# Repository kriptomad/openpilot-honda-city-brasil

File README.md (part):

# openpilot for the Honda City G7 (2023, Brazil)

[Versao em portugues: README.pt-BR.md](README.pt-BR.md)

An end-to-end, open effort to run openpilot / flowpilot on a 7th generation Honda City
(2023, Brazilian market, Honda Sensing camera-only "Bosch radarless", classic CAN, Bosch B
harness) using black panda class hardware (STM32F413), together with a from-scratch
**Hybrid Panda** PCB design (STM32H725, CAN-FD capable, black panda form factor) intended
as future hardware. The repository collects the hardware design, the panda firmware trees,
the car ports for two software stacks, the flashing procedure and every audit and report
produced along the way.

Author: Bruno Costa ([kriptomad](https://github.com/kriptomad)). This project is not
affiliated with, endorsed by or supported by comma.ai, Honda or any of the upstream authors.

**Nothing in this repository has been validated on real hardware or in a car.** Every
status below describes static analysis, compilation or continuous-integration results only.
No board has been fabricated, no panda has been flashed, no car has been fingerprinted.

## Status at a glance

| Track | Where | Status (honest) |
|---|---|---|
| Hybrid Panda PCB (STM32H725ZGT6, 4 layers) | [hardware/hybrid-panda](hardware/hybrid-panda) | Design complete and software-verified (2026-10-29): DRC 0 clearance / 0 unconnected / 0 shorts / 0 parity, 73 remaining items all intentional `lib_footprint_mismatch`; ERC 0 errors; gerber-rebuilt connectivity 0 short / 0 open; independent pin-by-pin review against the panda firmware. **Not physically verified**; bare-PCB order at the owner's discretion. Nothing built. |
| panda firmware `revive-f4` (black panda on current panda master) | [firmware/panda-revive-f4](firmware/panda-revive-f4) (submodule) | Compiles (debug and release), MISRA clean, `test.sh` green on the fork. Never executed on a board. |
| pandarevive (openpilot master host side for the black panda) | [docs/pandarevive.md](docs/pandarevive.md), repo [kriptomad/pandarevive](https://github.com/kriptomad/pandarevive) | openpilot branch `revive-f4` (4 commits on commaai master `0152aab4`): USB transport back in `pandad`, external panda flashing, tests. openpilot CI green on GitHub-hosted runners. Never executed on a board. |
| panda firmware `hybrid-h725` (Hybrid Panda target) | [firmware/panda-hybrid-h725](firmware/panda-hybrid-h725) (submodule) | Compiles (`panda_h7`, `panda_h7_hybrid`, `panda_h7_ldo`), MISRA clean. Never executed on a board (no board exists). |
| openpilot v0.9.9 Honda City port | [software/openpilot-v0.9.9-city-g7](software/openpilot-v0.9.9-city-g7) + [software/opendbc-v0.9.9-city-g7](software/opendbc-v0.9.9-city-g7) (submodules) | Port complete, two independent audits, CI green on the fork (static, build, unit, cars 0-3; process replay differs only by the expected `carParams.flags` bit). Untested in a car. |
| flowpilot standalone APK | [software/flowpilot-city-g7](software/flowpilot-city-g7) (submodule) | APK builds in GitHub Actions. Boots on a Samsung Galaxy S24 Ultra up to "waiting for controls" without a panda. Untested with a panda or a car. |
| Flashing guides | [docs/flashing](docs/flashing) | Written from the code and the PCB files. Not executed on hardware. |

## Safety disclaimer

This is an unvalidated, hobbyist research project. openpilot is a driver-assistance system
that requires the driver's full attention at all times; the ports and hardware in this
repository have not gone through comma.ai's validation, nor any other.

- Do not install any of this on a car that will be driven on public roads before completing
  bench tests (panda enumeration, `health()`, CAN loopback), passive CAN capture in the car
  with the car stationary, fingerprint confirmation and parking-lot tests with the system
  disengaged, in that order. The checklists live in
  [docs/flashing/flash-black-panda-city-g7.md](docs/flashing/flash-black-panda-city-g7.md)
  section 7 and [hardware/research/step9-bringup-e-teste-veiculo.md](hardware/research/step9-bringup-e-teste-veiculo.md).
- The Hybrid Panda PCB has never been manufactured. Its fabrication package is kept for
  review only; see [hardware/fabrication/readme.md](hardware/fabrication/readme.md).
- The firmware binaries are signed with comma's public debug key. They are development
  builds, not releases.
- You are solely responsible for what you do with this material. Check your local laws.

## Architecture overview

```mermaid
flowchart LR
    subgraph car [Honda City G7 2023 BR]
        cam[Honda Sensing camera, Bosch radarless]
        fcan[F-CAN / ACC-CAN, classic CAN 500 kbit/s]
    end
    harness[Honda Bosch B harness] --> box[Harness box, OpenpilotHardware/HarnessBox]
    cam --- harness
    fcan --- harness
    box --> bp[black panda, STM32F413, OpenpilotHardware BlackPanda v2]

    subgraph trackA [Track A: flowpilot]
        bp -->|USB OTG| phone[Android phone running the flowpilot APK]
    end

    subgraph trackB [Track B: openpilot v0.9.9]
        bp -.->|USB| op[Linux device running openpilot v0.9.9 City port]
    end

    subgraph future [Future hardware]
        hp[Hybrid Panda PCB, STM32H725, CAN-FD, hybrid-h725 firmware]
    end
    box -. same connector and harness .-> hp
```

- Track A (flowpilot): black panda flashed with the firmware built from the flowpilot tree
  (commaai/panda `abdc4185`), phone connected through USB OTG, flowpilot APK with the
  City G7 car layer. This is the path currently being prepared for first tests.
- Track B (openpilot v0.9.9): the last openpilot release that still supports the black panda
  natively, with the City G7 port backported from upstream opendbc, running on a Linux device.
- Future hardware: the Hybrid Panda PCB keeps the black panda form factor, connectors and
  harness, but carries an STM32H725 so the current red panda firmware (and its CAN-FD stack)
  can run on it. The City G7 is classic CAN, so this is not required for the car; it is a
  deliberate decision (D-05 in [docs/decisions.md](docs/decisions.md)).

## Repository map

| Path | Content |
|---|---|
| [README.md](README.md), [README.pt-BR.md](README.pt-BR.md) | This document and its Portuguese translation. |
| [LICENSE.md](LICENSE.md), [licenses/](licenses) | License inventory of every upstream source used, obligations, and the upstream license texts. |
| [docs/decisions.md](docs/decisions.md) | Decision log D-01 .. D-38 of the Hybrid Panda design (MCU choice, SMPS topology, straps, routing policy, deferred items). |
| [docs/final-report.md](docs/final-report.md) | Final report of the Hybrid Panda design protocol (STEP 1-9), premises P1-P11, risks, honesty lists. |
| [docs/final-audit.md](docs/final-audit.md) | Geometric final audit of the PCB (shorts, via-in-pad, hole hits, split nets). |
| [docs/progress.md](docs/progress.md) | Resume checkpoint of the design sessions (historical). |
| [docs/protocol-v3.md](docs/protocol-v3.md) | The working protocol the design followed (historical). |
| [docs/reference-sources.md](docs/reference-sources.md) | Upstream clones and pinned commits used as read-only references. |
| [docs/flashing/](docs/flashing) | Black panda flashing guide for the City G7 (EN and pt-BR). |
| [docs/pandarevive.md](docs/pandarevive.md) ([pt-BR](docs/pandarevive.pt-br.md)) | pandarevive: black panda on current openpilot master; what the panda and openpilot `revive-f4` branches restore, CI state, what is not done. Links to [kriptomad/pandarevive](https://github.com/kriptomad/pandarevive). |
| [docs/hardware/](docs/hardware) | Hybrid Panda hardware documentation: retrofit description, BOM (`bom.md` + `bom.csv`), schematic description, PCB fabrication specification (EN and pt-BR). Design only; not fabricated. |
| [docs/legacy-index.md](docs/legacy-index.md) | Generated index of the development repository with the old paths, kept for traceability. |
| [hardware/hybrid-panda/](hardware/hybrid-panda) | KiCad project: `HybridPanda.kicad_pcb`, `.kicad_sch`, `.kicad_pro`, local footprints (`.pretty`), 3D models, symbols; `snapshots/` holds the baseline and STEP 5 copies of the board. |
| [hardware/fabrication/](hardware/fabrication) | Gerbers, drill, assembly (BOM/CPL for JLCPCB), PDFs, STEP model, JLC zip. **Do not fabricate** (see its readme). |
| [hardware/reports/](hardware/reports) | DRC/ERC JSON reports, netlists, BOM, SI/PI audit, footprint-vs-datasheet audit, BOM audit, correction campaign log (`correcoes-aplicadas.md`, `corrections/`). |
| [hardware/research/](hardware/research) | Engineering research: hardware requirements extracted from the firmware (`hrs-red-panda.md`), coverage matrix, pin tables, STEP 3-9 documents, firmware port report (`hybrid-fw-port.md`), pandarevive scope, renders. |
| [hardware/scripts/](hardware/scripts) | KiCad Python / kicad-cli automation used to build, route, correct, validate and export the board, plus the DRC gate (`corr_gate.py`). |
| [hardware/reference/datasheets/](hardware/reference/datasheets) | STM32H725 datasheet (DS13313) and its extracted text. |
| [firmware/](firmware) | panda firmware: two submodules (`panda-revive-f4`, `panda-hybrid-h725`) and prebuilt black panda binaries in `prebuilt/`. See [firmware/readme.md](firmware/readme.md). |
| [software/](software) | Three submodules (openpilot v0.9.9 port, opendbc v0.9.9 port, flowpilot) plus the port documentation, patch series, audit tools and Windows test shims. See [software/readme.md](software/readme.md). |
| [archive/](archive) | Original OpenBlackPanda KiCad project the Hybrid Panda derives from (`baseline-original/`) and the SHA-256 manifests of the development tree (`manifests/`). See [archive/readme.md](archive/readme.md). |

## Quick start per track

### A. Install the flowpilot APK

1. Download `flowpilot-city-g7-brazil-ffd228c.apk` from this repository's release
   [v0.1-city-g7-brazil](https://github.com/kriptomad/openpilot-honda-city-brasil/releases/tag/v0.1-city-g7-brazil)
   (mirror of the build published in
   [kriptomad/flowpilot-city-g7](https://github.com/kriptomad/flowpilot-city-g7/releases/tag/v0.1-city-g7-brazil)).
2. Verify the hash before installing:
   `SHA256 493891cd62d3f2eaf094e414489d7b0dae8bde297a673c305fba6eef298d4adb`
   (235,399,803 bytes).
3. Install with `adb install -r flowpilot-city-g7-brazil-ffd228c.apk` (or from the file
   manager with unknown sources allowed), disable battery optimisation for the app, grant
   camera, location and USB permissions.
4. In the app settings select the car `HONDA CITY 7G` (param `Mycar`). Details, device
   requirements and the list of what is not verified:
   [software/flowpilot-port/port-city-flowpilot.md](software/flowpilot-port/port-city-flowpilot.md)
   sections 8 to 10.

### B. Flash the black panda

Full guide: [docs/flashing/flash-black-panda-city-g7.md](docs/flashing/flash-black-panda-city-g7.md)
([pt-BR](docs/flashing/flash-black-panda-city-g7.pt-br.md)). Summary for the flowpilot track:

1. Hardware: Loetkolben OpenpilotHardware BlackPanda v2 (STM32F413RGT6). `SW1` pulls
   `BOOT0` high: hold it while plugging the USB-C cable to enter the ST DFU bootloader
   (`0483:df11`). On Windows bind WinUSB with Zadig for `0483:df11`, `bbaa:ddee` and
   `bbaa:ddcc`.
2. Python side: `pip install libusb1 pyusb` and run from the flowpilot tree
   ([software/flowpilot-city-g7](software/flowpilot-city-g7)), so that the `panda` package
   matches the firmware.
3. Write the bootstub: `python -c "from panda import PandaDFU; PandaDFU(None).recover()"`.
   The board re-enumerates as `bbaa:ddee`.
4. Write the application:
   `python -c "from panda import Panda; Panda().flash(fn=r'firmware/prebuilt/flowpilot-black-panda/panda.bin.signed')"`
   (path relative to this repository). The board re-enumerates as `bbaa:ddcc`.
5. Check: `python -c "from panda import Panda; p=Panda(); print(p.get_type(), p.get_version())"`
   should print `b'\x03' DEV-a2f1983c-DEBUG`.

The three firmware trees are not interchangeable; see [Firmware](#firmware) below before
choosing one.

### C. Build the openpilot v0.9.9 port

```
git clone --recurse-submodules -b v0.9.9-cityg7-blackpanda https://github.com/kriptomad/openpilot
cd openpilot
scons -j$(nproc)      # also builds panda/board (F4 and H7) with the Honda Bosch radarless safety
```

Or initialise the submodule in this repository:
`git submodule update --init --recursive software/openpilot-v0.9.9-city-g7` (large: the
openpilot tree with its submodules is well above 1 GB). `pandad` flashes the panda by itself
at start-up. Port notes, validation and bench checklist:
[software/openpilot-port/readme.md](software/openpilot-port/readme.md).

### D. Open the Hybrid Panda KiCad project

- Open [hardware/hybrid-panda/HybridPanda.kicad_pro](hardware/hybrid-panda/HybridPanda.kicad_pro)
  with KiCad 10 (the board file format is 20260206, saved with KiCad 10.0.7; KiCad 8/9 will
  not load the PCB).
- Final DRC/ERC: [hardware/reports/hybrid_DRC_final.json](hardware/reports/hybrid_DRC_final.json),
  [hardware/reports/hybrid_ERC_final.json](hardware/reports/hybrid_ERC_final.json);
  per-step reports under [hardware/reports/corrections/](hardware/reports/corrections).
- Fabrication outputs (review only): [hardware/fabrication/](hardware/fabrication).
- Re-running the pipeline requires KiCad 10's bundled Python and the paths configured in
  [hardware/scripts/hp_common.py](hardware/scripts/hp_common.py); see
  [hardware/scripts/readme.md](hardware/scripts/readme.md).

## The car: Honda City G7 2023 (Brazil)

Facts as used by the ports (sources: upstream opendbc commit `43006b9a`, PR commaai/opendbc #2425,
and the City route `56b2cf1dacdcd033|00000017--d24ffdb376`; details in
[software/openpilot-port/readme.md](software/openpilot-port/readme.md) and
[software/flowpilot-port/port-city-flowpilot.md](software/flowpilot-port/port-city-flowpilot.md)):

- Platform `HONDA_CITY_7G`, `HondaBoschPlatformConfig` with flag `BOSCH_RADARLESS`
  (camera-only Honda Sensing). Classic CAN, **not** CAN-FD (premise P1 of the Hybrid Panda
  project was refuted by this fact; see [hardware/research/p1-veiculo-honda-city-2023.md](hardware/research/p1-veiculo-honda-city-2023.md)).
- Harness: Honda Bosch **B**. Safety: `SAFETY_HONDA_BOSCH` with the `RADARLESS` parameter
  (value 8); TX messages 0xE4, 0x1C8, 0x30C, 0x33D; no longitudinal control (the stock ACC
  keeps controlling speed).
- DBC `honda_civic_ex_2022_can_generated`; `STEER_THRESHOLD` 600; torque lateral tuning
  `[1.2, 1.2, 0.23]` with `ki` 0.3; `steerActuatorDelay` 0.15 s; `minSteerSpeed` from
  CarParams (23 km/h in the flowpilot port, 14 mph in `CARS.md`).
- Transmission: conventional CVT reported through `GEARBOX` (0x191) with the upstream
  `GEARBOX_CVT` layout (`1 P 2 R 3 N 4 D 7 L 10 S`); the `S` position is accepted.
- No electric parking brake: the car does not send `EPB_STATUS` (0x1C2). The v0.9.9 code
  required it at 50 Hz for every Bosch car, which would time out the CAN parser; the upstream
  `HAS_EPB` detection (commit `6fa346ed`) was backported, including the DBC move of
  `EPB_STATUS` to `_honda_common.dbc`.
- Firmware fingerprint: 6 ECUs (eps, gateway, srs, fwdRadar, vsa, transmission) identical to
  upstream; the flowpilot port additionally carries a 36-message CAN fingerprint for bus 0.

## Hardware: Hybrid Panda

Goal: a board in the black panda form factor (same connectors, same harness box, same
OpenBlackPanda power stage) that runs the official red panda firmware without modification,
on an **STM32H725ZGT6 (LQFP-144, Direct SMPS)**, keeping the four TJA1042TK/3 transceivers
(CAN FD up to 5 Mbit/s). Decisions with their reasoning are in
[docs/decisions.md](docs/decisions.md); the state of the whole design is in
[docs/final-report.md](docs/final-report.md).

What differs from a red panda and from the OpenBlackPanda baseline:

- MCU STM32H725ZGT6 instead of STM32F413 (D-02); 1 MB flash required by the firmware (P9);
  LQFP-144 because the firmware needs port F/G pins and configures Direct SMPS on that
  package (P7). The MCU is mounted on the bottom side (D-21).
- HW_TYPE straps: PF7-PF10 low so the upstream firmware detects `HW_TYPE_RED_PANDA`
  (D-08); PF9 on solder jumper `JP1` to select the `HW_TYPE_HYBRID_PANDA` id added by the
  `hybrid-h725` firmware (D-35).
- GPS module removed (D-03); no 120 ohm termination (D-04); SBU to ADC through 10 kohm series
  and BAT54S clamp on PC4/PA1 (D-12/D-16); transceiver STB with external pull-up (D-09);
  VFBSMPS tied to VCAP as the Direct SMPS topology requires (D-35, found by the firmware
  port and the SI/PI audit).
- Board grown +5 mm south and +3 mm east (D-24, D-33): 50.625 x 46.75 mm; the original
  enclosure files no longer fit.
- Firmware parity check: all 36 pins required by the red panda firmware land on the expected
  pins of U7 (`parity_red_h7`, 36/36). The pandarevive and hybrid firmware reports are in
  [hardware/research/hybrid-fw-port.md](hardware/research/hybrid-fw-port.md).

Current numbers (after the post-audit correction campaign, see
[hardware/reports/correcoes-aplicadas.md](hardware/reports/correcoes-aplicadas.md)):

| Check | Result |
|---|---|
| DRC total | 182 -> 135 -> 73 items (verification pass 2026-10-29) |
| DRC blocking categories | clearance 0, unconnected 0, schematic parity 0, shorting items 0, tracks crossing 0, courtyard 0 |
| DRC remaining | lib_footprint_mismatch 73 only (footprints edited locally on purpose, ~61 graphics/3D-path differences); hole_clearance, silk and text_height items fixed |
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
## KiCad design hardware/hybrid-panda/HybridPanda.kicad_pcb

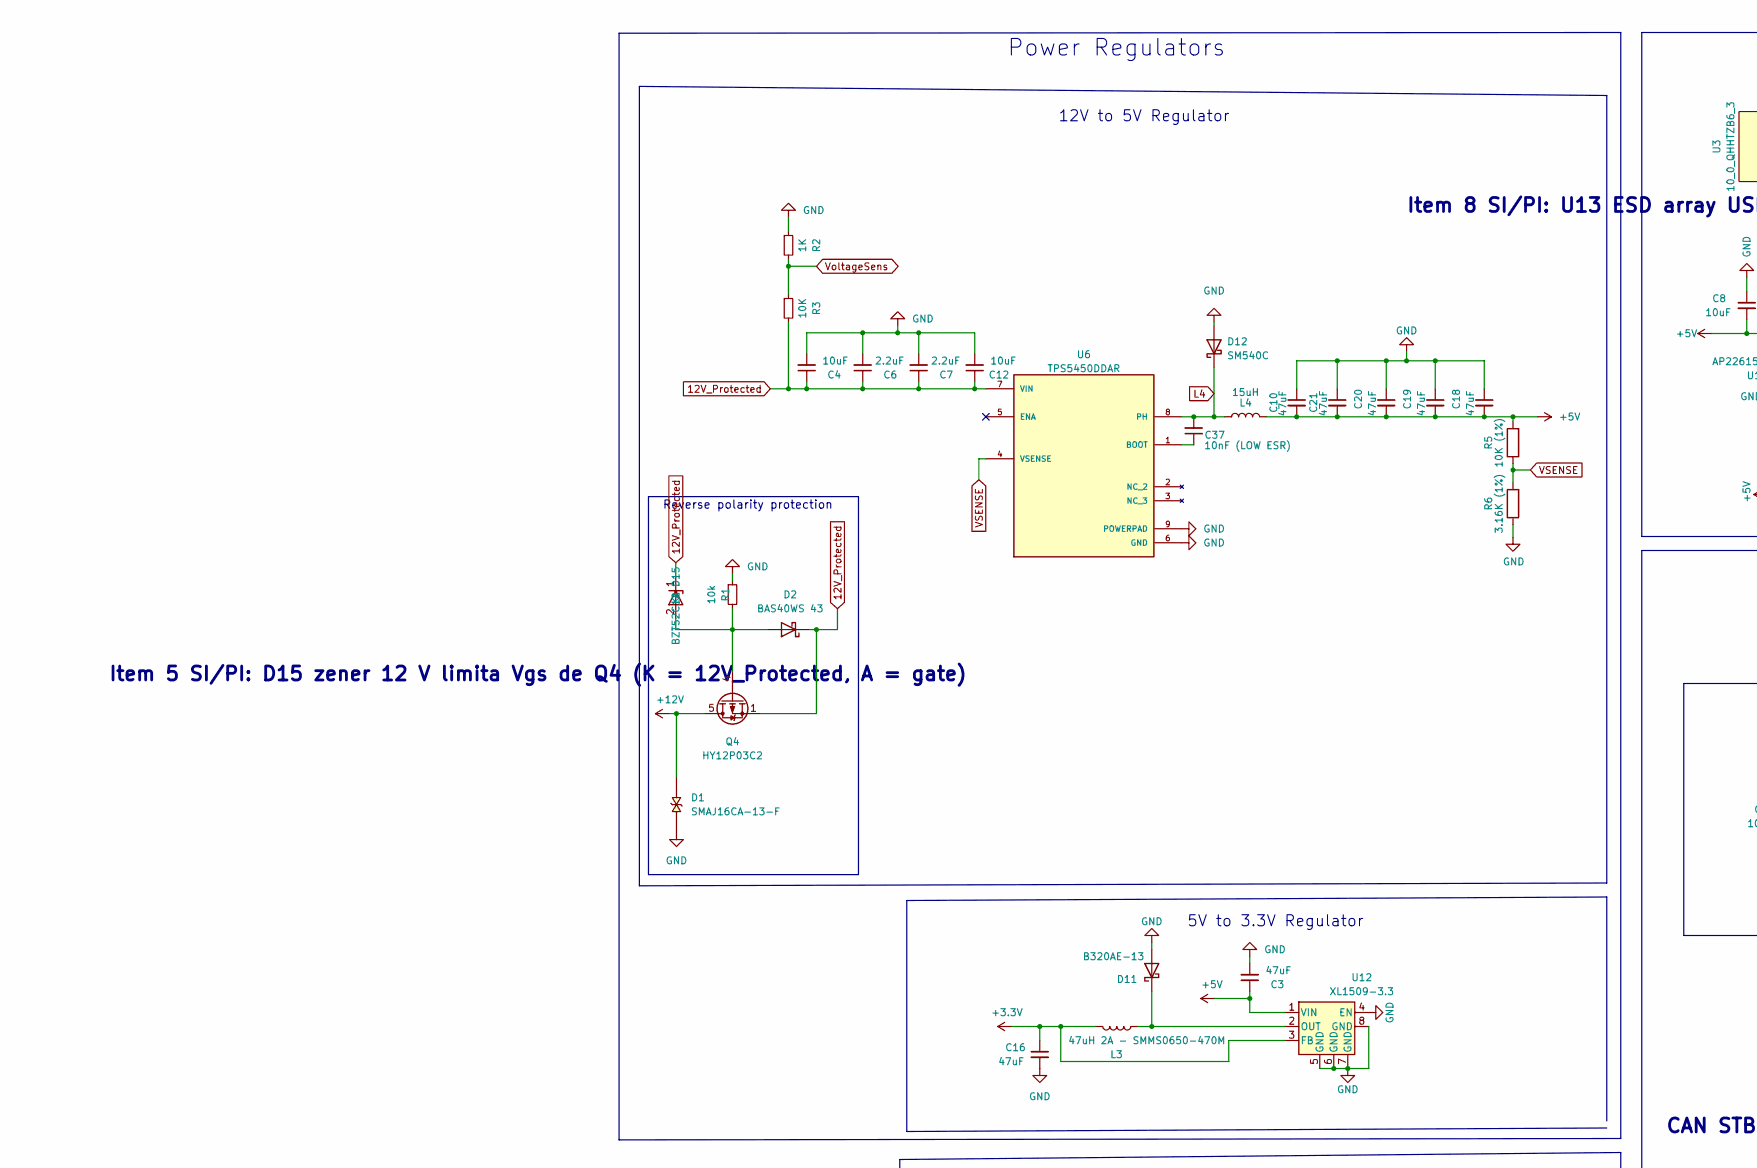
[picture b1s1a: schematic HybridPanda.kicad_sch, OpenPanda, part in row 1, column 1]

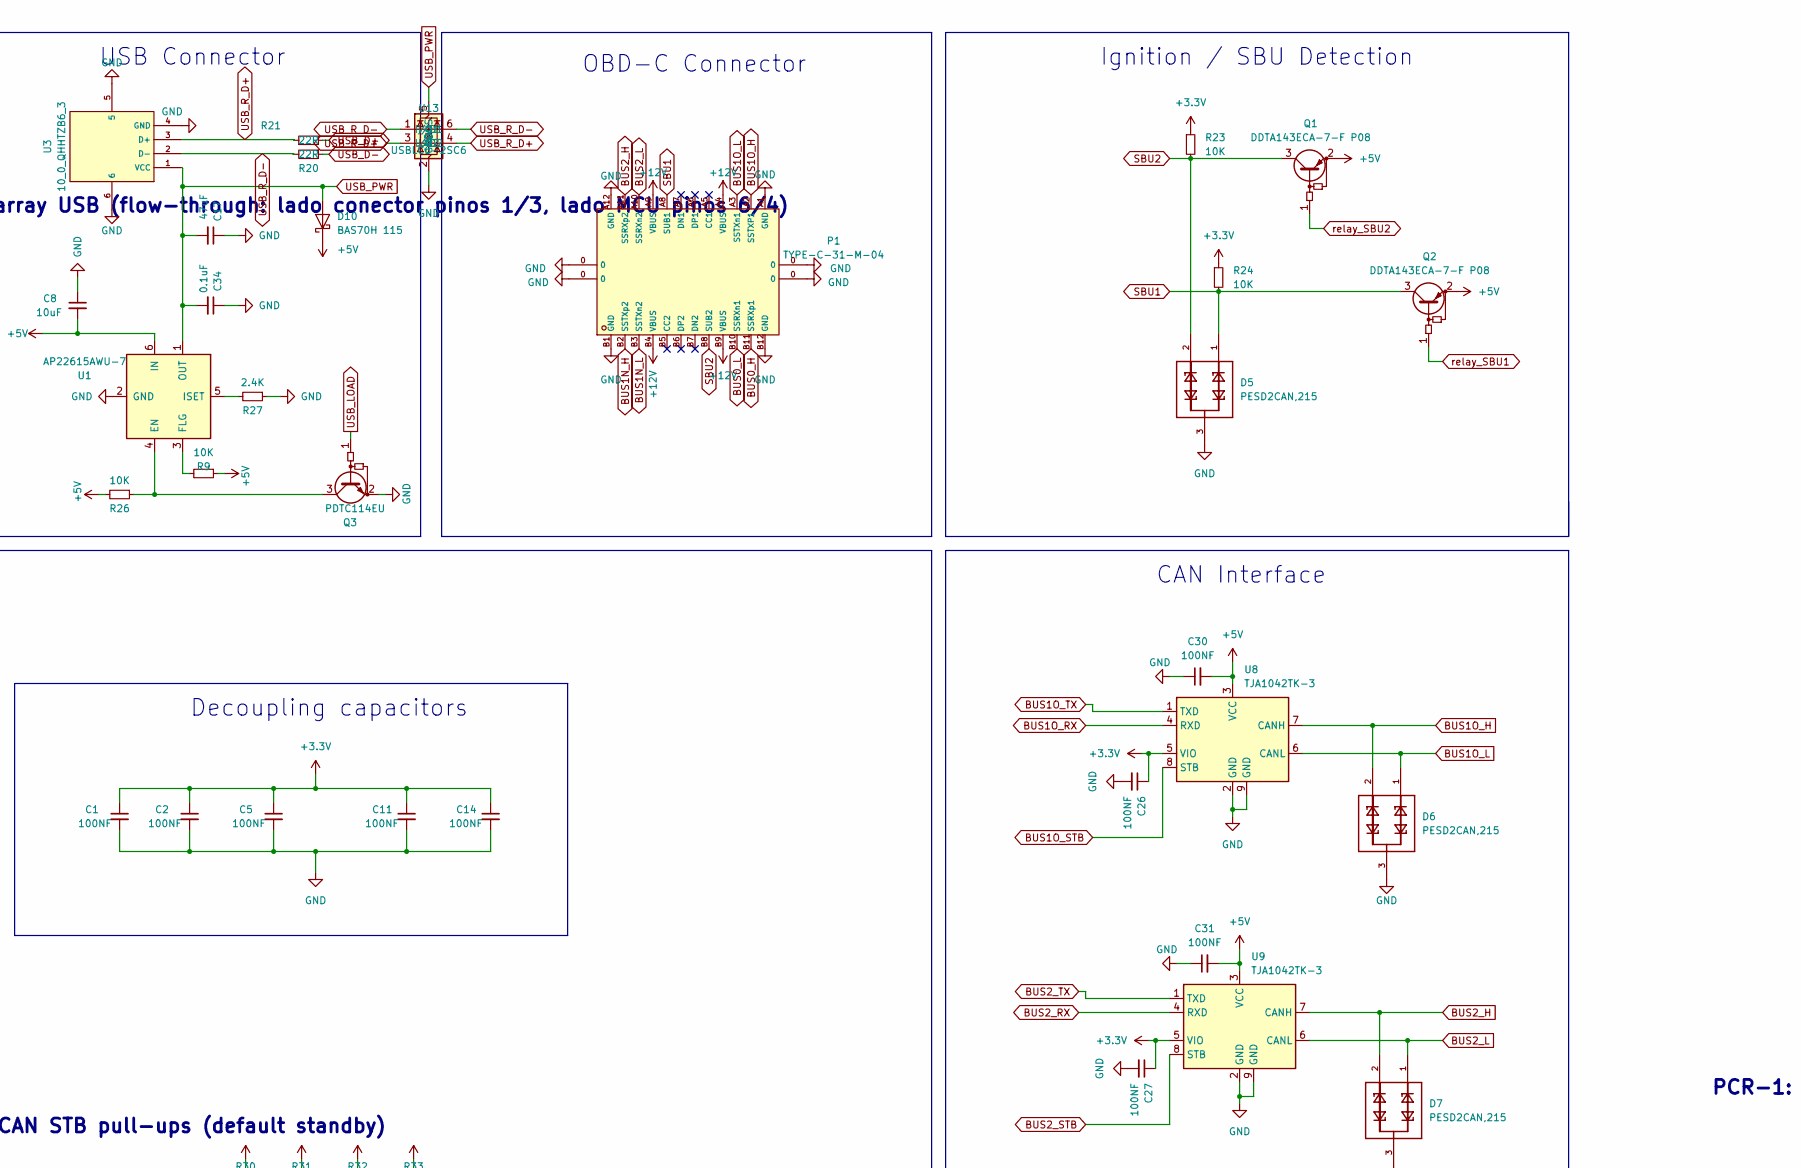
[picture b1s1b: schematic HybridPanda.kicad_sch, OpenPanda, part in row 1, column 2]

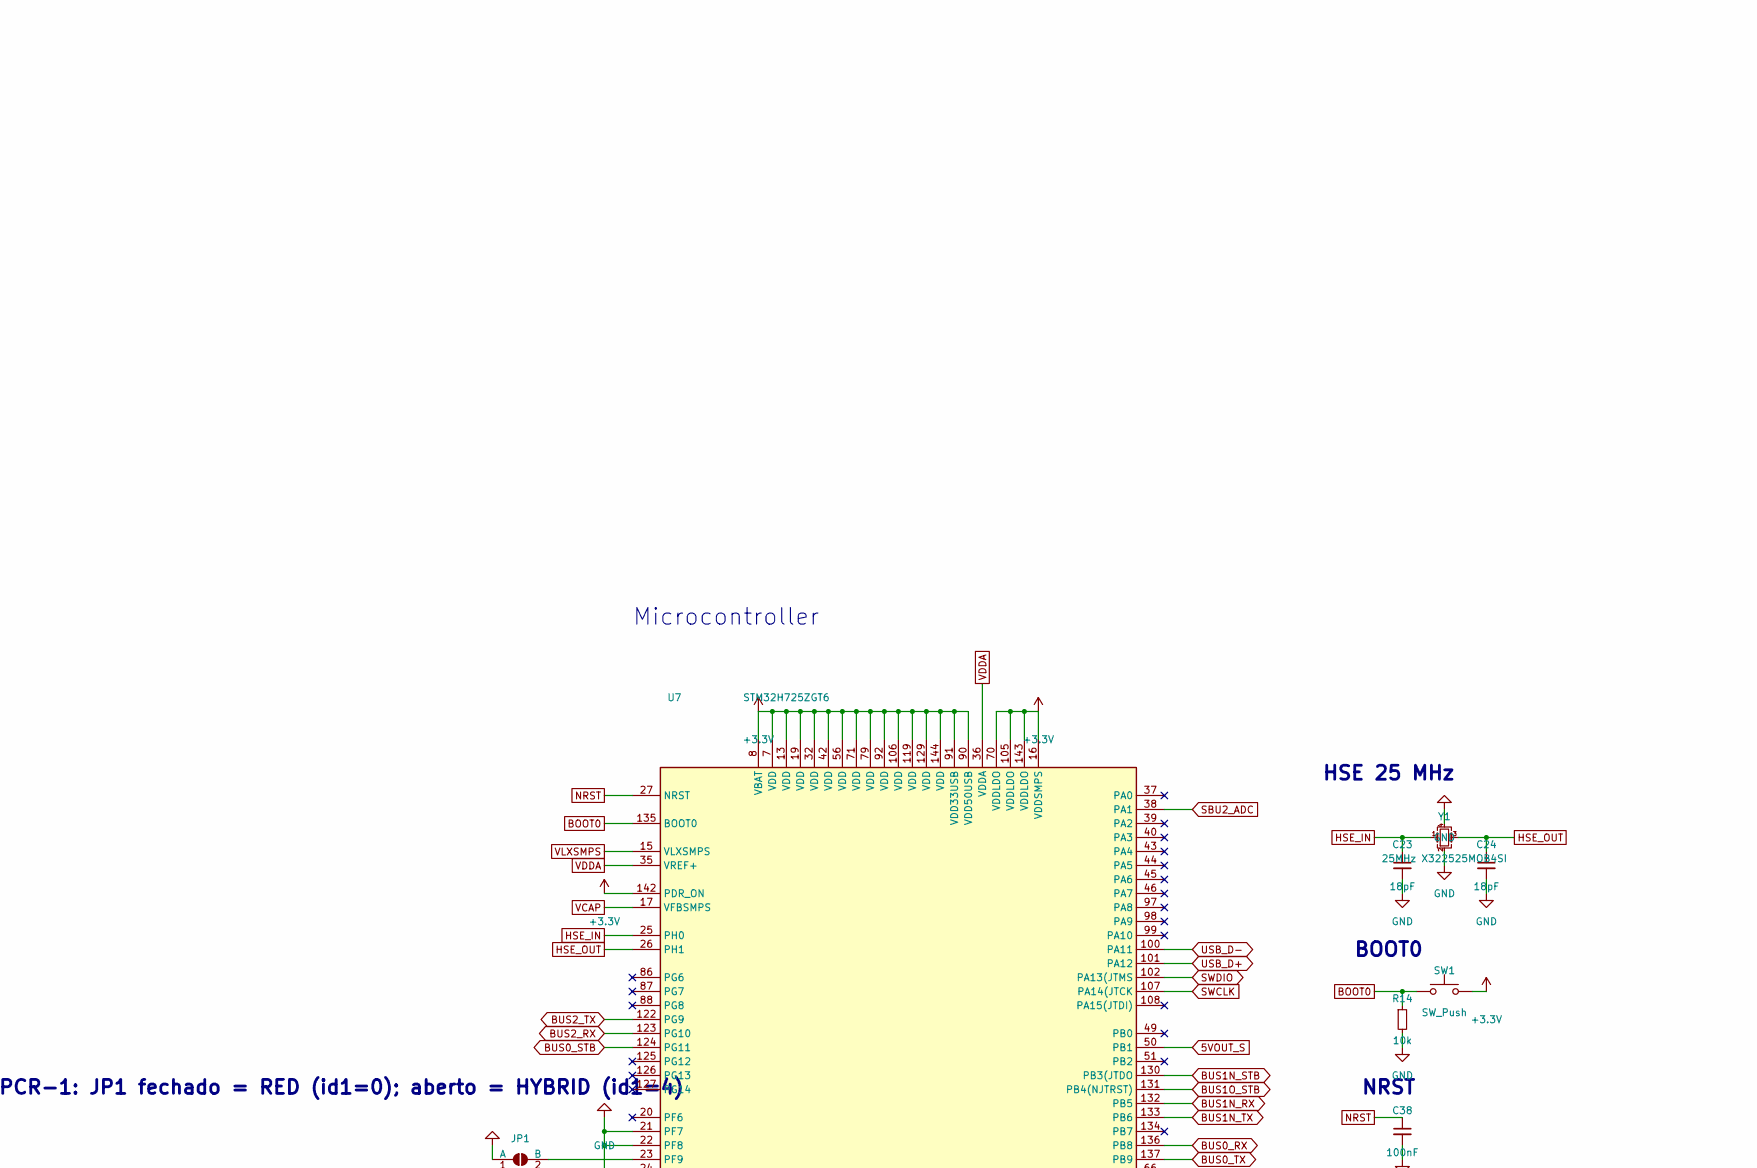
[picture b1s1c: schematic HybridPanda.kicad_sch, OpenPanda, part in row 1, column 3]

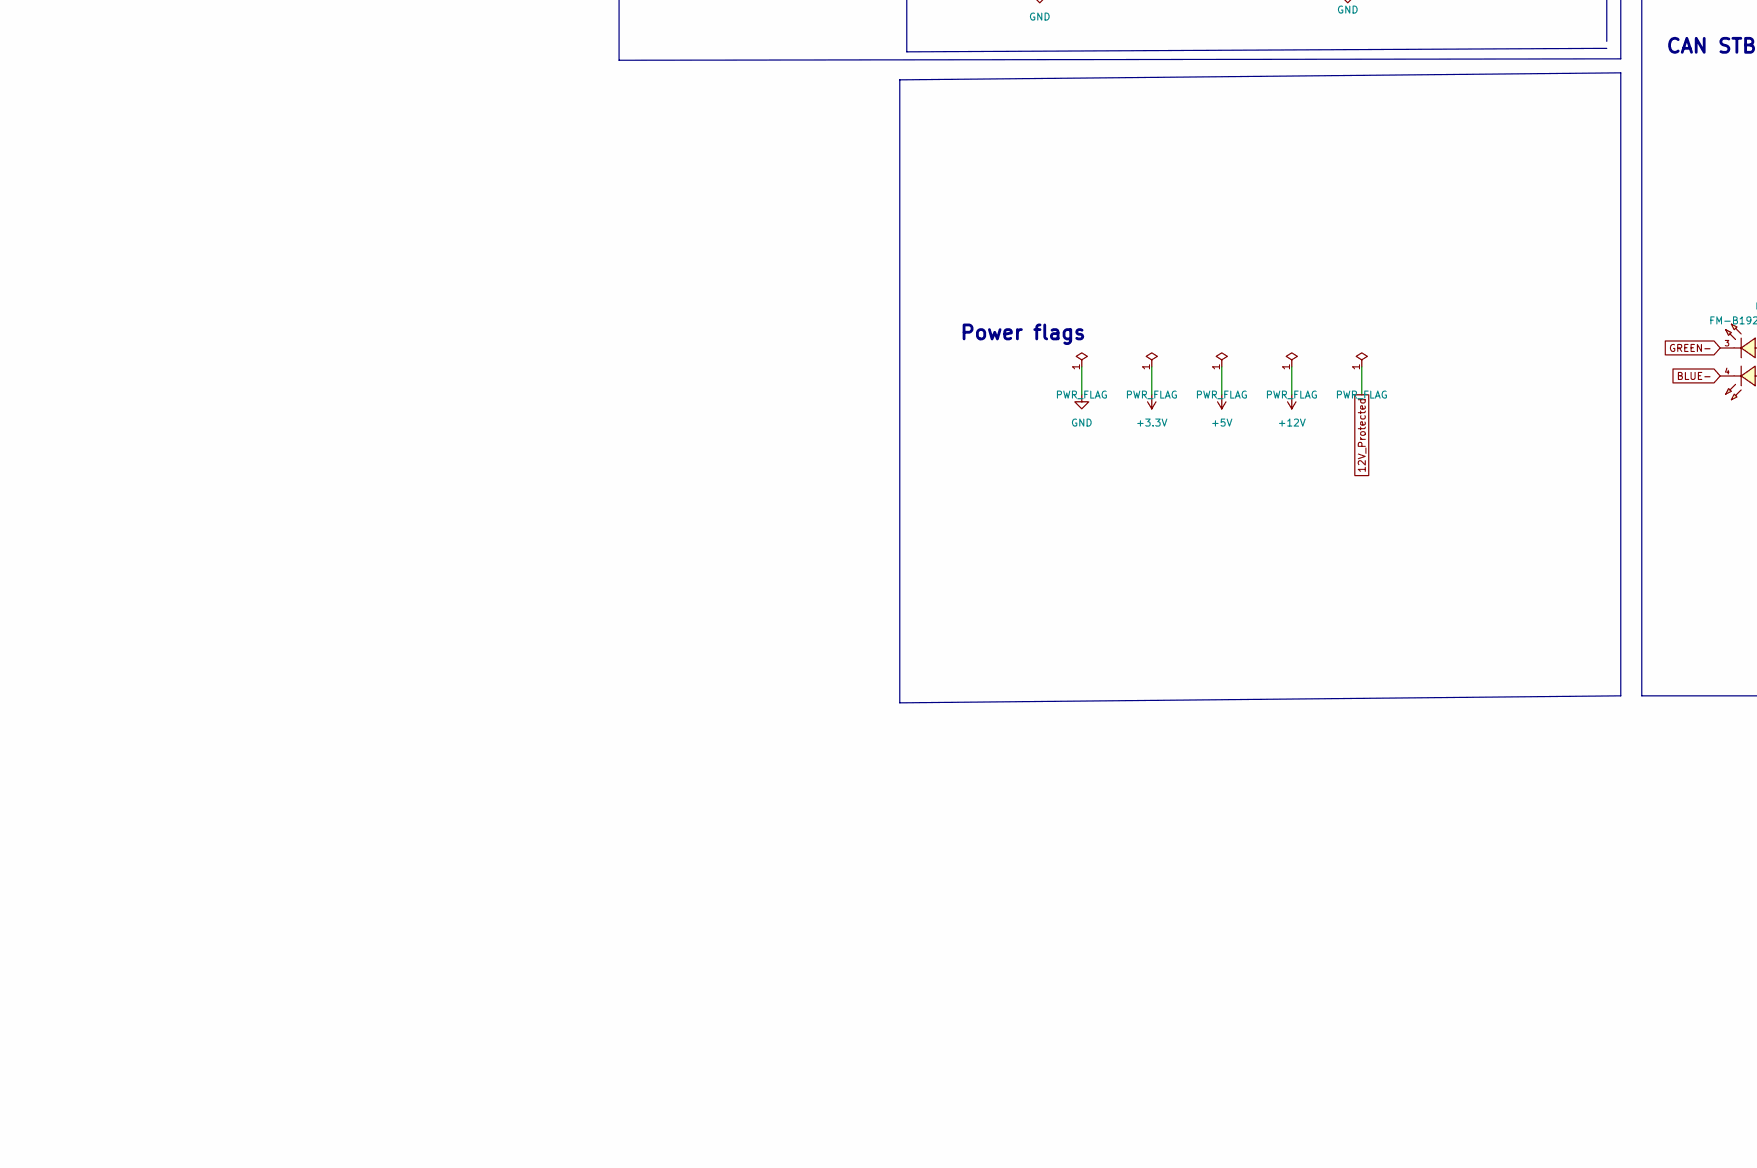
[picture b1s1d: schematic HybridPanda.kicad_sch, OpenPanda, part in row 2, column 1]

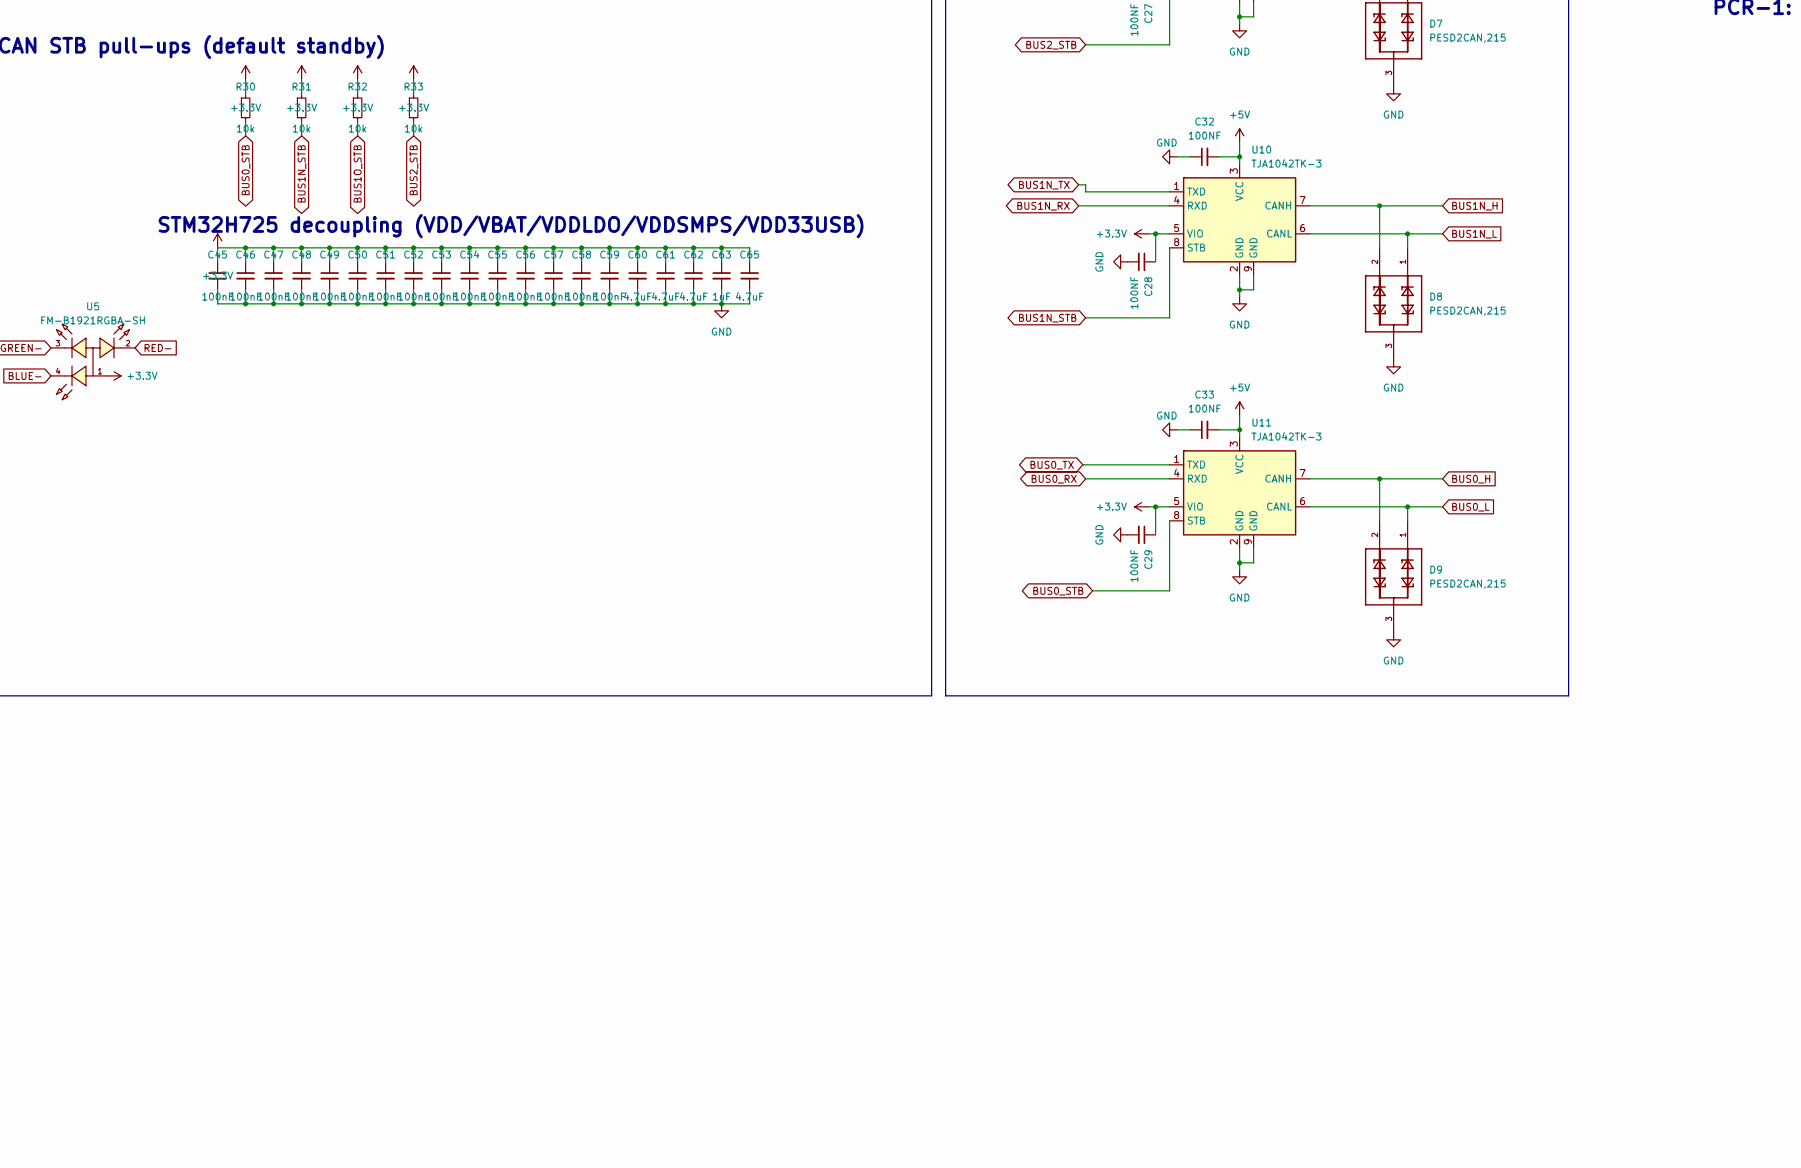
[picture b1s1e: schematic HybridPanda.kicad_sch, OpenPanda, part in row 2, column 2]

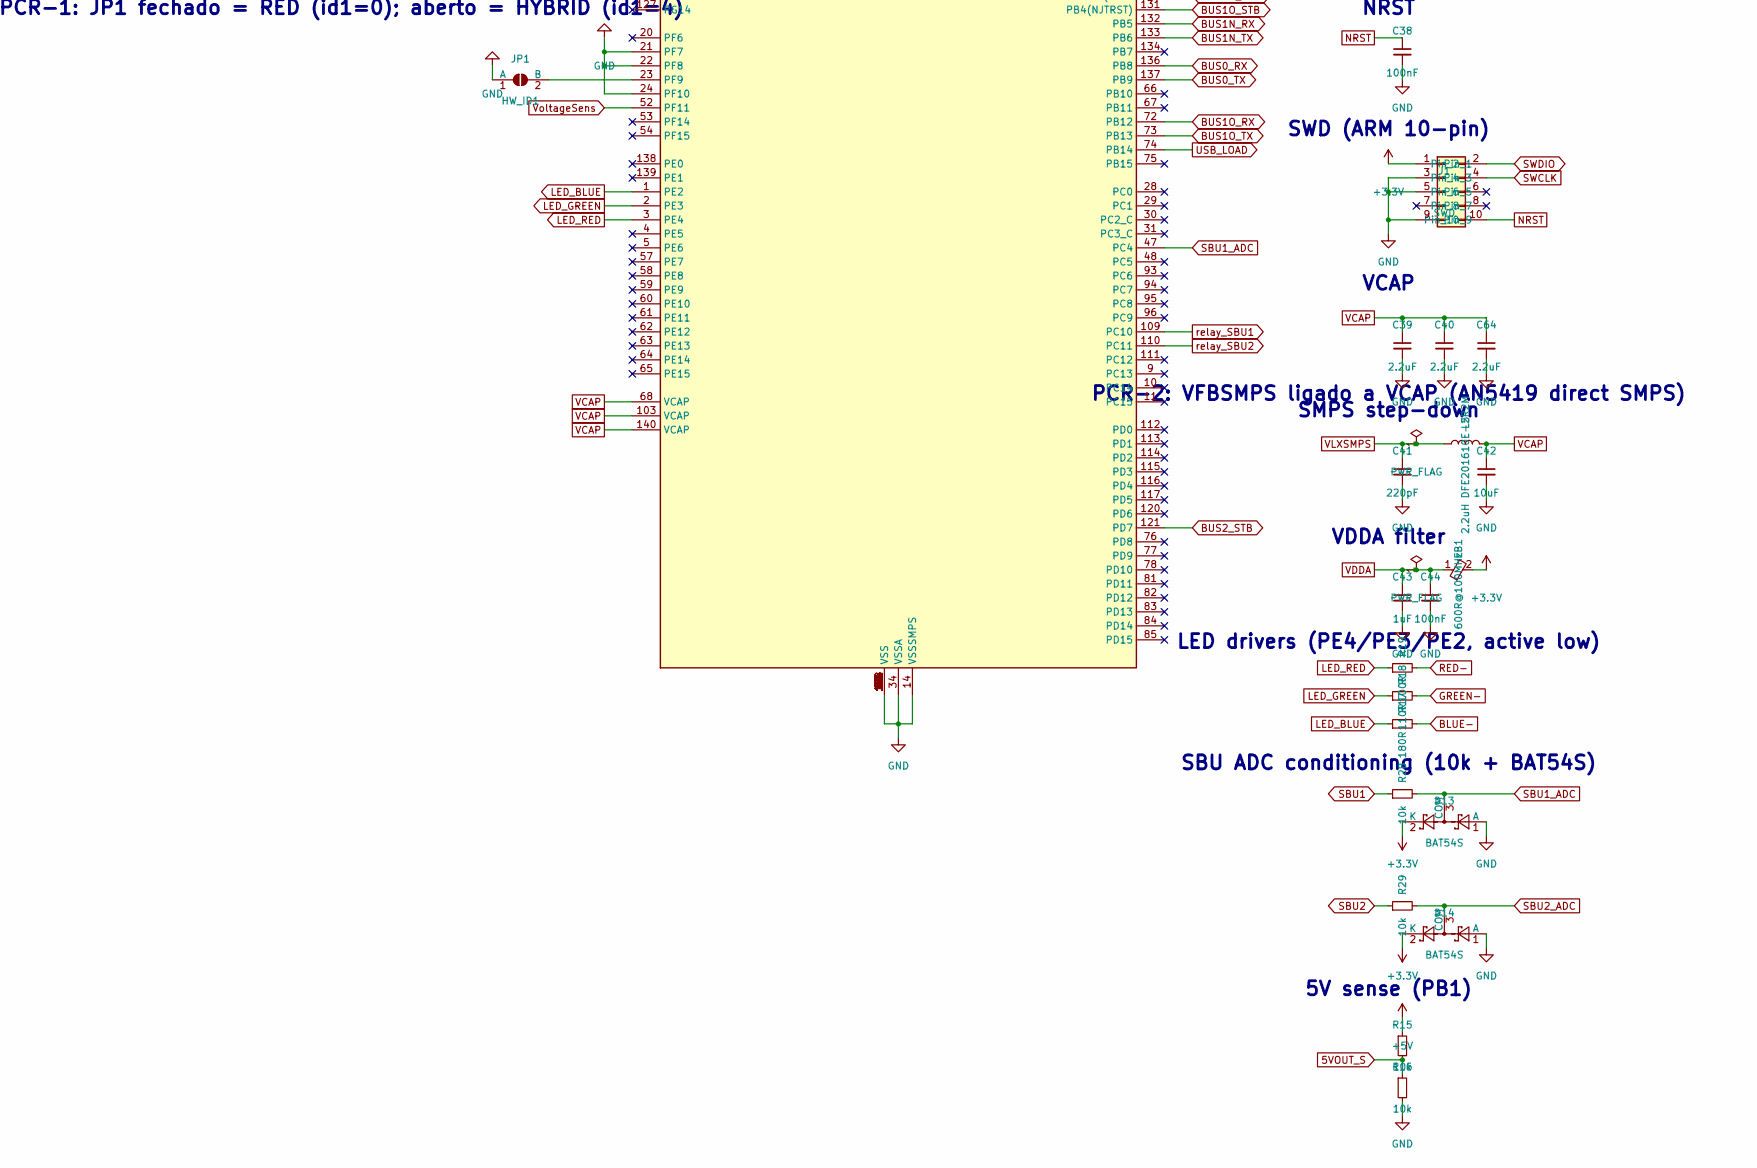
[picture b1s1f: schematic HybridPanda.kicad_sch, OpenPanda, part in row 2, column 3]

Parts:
C1, C2, C5, C11, C14, C26, C27, C28, C29, C30, C31, C32, C33: 100NF; C_0402_1005Metric; MPN CL05B104KB54PNC; LCSC C307331
C3, C10, C16, C17, C18, C19, C20, C21: 47uF; C_0805_2012Metric; MPN 0805X476M100NT; LCSC C178332
C4, C12: 10uF; C_0805_2012Metric; MPN CL21A106KBYQNNE; LCSC C2932476
C6, C7: 2.2uF; C_0805_2012Metric; MPN CC0805KKX7R9BB225; LCSC C125847
C8: 10uF; C_0402_1005Metric; MPN CL05A106MP5NUNC; LCSC C315248
C23, C24: 18pF; C_0402_1005Metric; MPN 0402CG180J500NT; LCSC C1549
C34: 0.1uF; C_0402_1005Metric; MPN CL05B104KB54PNC; LCSC C307331
C37: 10nF (LOW ESR); C_0402_1005Metric; MPN CL05B103KB5NNNC; LCSC C15195
C38, C44, C45, C46, C47, C48, C49, C50, C51, C52, C53, C54, C55, C56, C57, C58, C59: 100nF; C_0402_1005Metric; MPN CL05B104KB54PNC; LCSC C307331
C39, C40: 2.2uF; C_0603_1608Metric; MPN CL10A225KO8NNNC; LCSC C23630
C41: 220pF; C_0402_1005Metric; MPN 0402B221K500NT; LCSC C1530
C42: 10uF; C_0805_2012Metric; MPN CL21A106KAYNNNE; LCSC C15850
C43, C63: 1uF; C_0402_1005Metric; MPN CL05A105KA5NQNC; LCSC C52923
C60, C61, C62, C65: 4.7uF; C_0603_1608Metric; MPN CL10A475KO8NNNC; LCSC C19666
C64: 2.2uF; C_0402_1005Metric; MPN CL05A225MQ5NSNC; LCSC C12530
D1: SMAJ16CA-13-F; DIOM4325X250N; PARTREV S2102; LCSC C148217
D2: BAS40WS 43; D_SOD-323; MPN BAS40WS 43; LCSC C22648
D5, D6, D7, D8, D9: PESD2CAN,215; SOT95P230X110-3N; MPN PESD2CAN,215; LCSC C75176
D10: BAS70H 115; D_SOD-123F; MPN BAS70H,115; LCSC C426766
D11: B320AE-13; D_SMA; MPN B340A-13-F; LCSC C85098
D12: SM540C; D_SMC; MPN B540C-13-F; LCSC C72264
D13, D14: BAT54S; SOT-23; MPN BAT54S,215; LCSC C47546
D15: BZT52C12; D_SOD-123; MPN BZT52C12; LCSC C571379
FB1: 600R@100MHz; L_0603_1608Metric; MPN GZ1608D601TF; LCSC C1002
J1: SWD; PinHeader_2x05_P1.27mm_Vertical_SMD; MPN 20021121-00010C4LF; LCSC C150517
JP1: HW_ID1; SolderJumper-2_P1.3mm_Open_Pad1.0x1.5mm
L3: 47uH 2A - SMMS0650-470M; IND-SMD_L7.3-W6.8; MPN SMMS0650-470M; JLCPCB C149588
L4: 15uH; L_10.5x11.5_H4.0; MPN MWSA1004S-150MT; LCSC C151872
L5: 2.2uH DFE201610E-2R2M; L_Murata_DFE201610P; MPN DFE201610E-2R2M=P2; LCSC C337891
P1: TYPE-C-31-M-04; USB-C-SMD_TYPE-C-USB-20; MPN TYPE-C-31-M-04; LCSC C129018
Q1, Q2: DDTA143ECA-7-F P08; SOT23-3; MPN DDTA143ECA-7-F; LCSC C460029
Q3: PDTC114EU; SOT-323_SC-70; MPN PDTC114EU,115; LCSC C135830
Q4: HY12P03C2; PowerPAK_SO-8_Single; MPN HY12P03C2; LCSC C358006
R1: 10k; R_0603_1608Metric; MPN 0603WAF1002T5E; LCSC C25804
R2: 1K; R_0402_1005Metric; MPN 0402WGF1001TCE; LCSC C11702
R3, R9, R23, R24, R26: 10K; R_0402_1005Metric; MPN 0402WGF1002TCE; LCSC C25744
R5: 10K (1%); R_0402_1005Metric; MPN 0402WGF1002TCE; LCSC C25744
R6: 3.16K (1%); R_0603_1608Metric; MPN 0603WAF3161T5E; LCSC C22993
R14, R15, R16, R28, R29, R30, R31, R32, R33: 10k; R_0402_1005Metric; MPN 0402WGF1002TCE; LCSC C25744
R17: 180R; R_0402_1005Metric; MPN 0402WGF1800TCE; LCSC C38941
R18: 110R; R_0402_1005Metric; MPN ERJ2RKF1100X; LCSC C413064
R19: 100R; R_0402_1005Metric; MPN 0402WGF1000TCE; LCSC C25076
R20, R21: 22R; R_0402_1005Metric; MPN 0402WGF220JTCE; LCSC C25092
R27: 2.4K; R_0402_1005Metric; MPN 0402WGF2401TCE; LCSC C25882
SW1: SW_Push; SW_SPST_SKQG_WithStem; MPN SKQGAFE010; LCSC C202424
U1: AP22615AWU-7; SOT-23-6; MPN AP22615AWU-7
U3: 10_0_QHHTZB6_3; USB-A-TH_10.0QHHTZB6.3; MPN 10.0 QHHTZB6.3; LCSC C668591
U5: FM-B1921RGBA-SH; LED-ARRAY-SMD_4P-L2.2-W2.1-BR; MPN FM-B1921RGBA-SH; LCSC C727904
U6: TPS5450DDAR; CONV_TPS5450DDAR; PARTREV D; LCSC C114425
U7: STM32H725ZGT6; LQFP-144_20x20mm_P0.5mm; MPN STM32H725ZGT6; LCSC C730156
U8, U9, U10, U11: TJA1042TK-3; DFN-8-1EP_3x3mm_P0.65mm_EP1.55x2.4mm; MPN TJA1042TK/3/1J; LCSC C131480
U12: XL1509-3.3; Diodes_PSOP-8; MPN XL1509-3.3E1; LCSC C74193
U13: USBLC6-2SC6; SOT-23-6; MPN USBLC6-2SC6; LCSC C7519
Y1: 25MHz X322525MOB4SI; Crystal_SMD_3225-4Pin_3.2x2.5mm; MPN X322525MOB4SI; LCSC C9006

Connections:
5VOUT_S: R15.2, R16.1, U7.50 (PB1)
12V_Protected: C4.1, C6.1, C7.1, C12.1, D2.1 (K), D15.1 (K), Q4.1 (S), Q4.2 (S), Q4.3 (S), R3.2, U6.7 (VIN)
+3V3: C1.1, C2.1, C5.1, C11.1, C14.1, C16.1, C26.1, C27.1, C28.1, C29.1, C45.1, C46.1, C47.1, C48.1, C49.1, C50.1, C51.1, C52.1, C53.1, C54.1, C55.1, C56.1, C57.1, C58.1, C59.1, C60.1, C61.1, C62.1, C63.1, C65.1, D13.2 (K), D14.2 (K), FB1.2, J1.1, L3.2, R23.1, R24.1, R30.1, R31.1, R32.1, R33.1, SW1.2, U5.1 (+), U7.7 (VDD), U7.8 (VBAT), U7.13 (VDD), U7.16 (VDDSMPS), U7.19 (VDD), U7.32 (VDD), U7.42 (VDD), U7.56 (VDD), U7.70 (VDDLDO), U7.71 (VDD), U7.79 (VDD), U7.90 (VDD50USB), U7.91 (VDD33USB), U7.92 (VDD), U7.105 (VDDLDO), U7.106 (VDD), U7.119 (VDD), U7.129 (VDD), U7.142 (PDR_ON), U7.143 (VDDLDO), U7.144 (VDD), U8.5 (VIO), U9.5 (VIO), U10.5 (VIO), U11.5 (VIO), U12.3 (FB)
+5V: C3.1, C8.2, C10.2, C18.2, C19.2, C20.2, C21.2, C30.2, C31.2, C32.2, C33.2, D10.1 (K), L4.2, Q1.2 (E), Q2.2 (E), R5.2, R9.1, R15.1, R26.2, U1.6 (IN), U8.3 (VCC), U9.3 (VCC), U10.3 (VCC), U11.3 (VCC), U12.1 (VIN)
+12V: D1.2, P1.A4 (VBUS), P1.A9 (VBUS), P1.B4 (VBUS), P1.B9 (VBUS), Q4.5 (D)
BLUE-: R17.2, U5.4 (B-)
BOOT0: R14.1, SW1.1, U7.135 (BOOT0)
BUS0_H: D9.2, P1.B11 (SSRXp1), U11.7 (CANH)
BUS0_L: D9.1, P1.B10 (SSRXn1), U11.6 (CANL)
BUS0_RX: U7.136 (PB8), U11.4 (RXD)
BUS0_STB: R30.2, U7.124 (PG11), U11.8 (STB)
BUS0_TX: U7.137 (PB9), U11.1 (TXD)
BUS1N_H: D8.2, P1.B2 (SSTXp2), U10.7 (CANH)
BUS1N_L: D8.1, P1.B3 (SSTXn2), U10.6 (CANL)
BUS1N_RX: U7.132 (PB5), U10.4 (RXD)
BUS1N_STB: R31.2, U7.130 (PB3(JTDO), U10.8 (STB)
BUS1N_TX: U7.133 (PB6), U10.1 (TXD)
BUS1O_H: D6.2, P1.A2 (SSTXP1), U8.7 (CANH)
BUS1O_L: D6.1, P1.A3 (SSTXn1), U8.6 (CANL)
BUS1O_RX: U7.72 (PB12), U8.4 (RXD)
BUS1O_STB: R32.2, U7.131 (PB4(NJTRST)), U8.8 (STB)
BUS1O_TX: U7.73 (PB13), U8.1 (TXD)
BUS2_H: D7.2, P1.A11 (SSRXp2), U9.7 (CANH)
BUS2_L: D7.1, P1.A10 (SSRXn2), U9.6 (CANL)
BUS2_RX: U7.123 (PG10), U9.4 (RXD)
BUS2_STB: R33.2, U7.121 (PD7), U9.8 (STB)
BUS2_TX: U7.122 (PG9), U9.1 (TXD)
GND: C1.2, C2.2, C3.2, C4.2, C5.2, C6.2, C7.2, C8.1, C10.1, C11.2, C12.2, C14.2, C16.2, C17.1, C18.1, C19.1, C20.1, C21.1, C23.2, C24.2, C26.2, C27.2, C28.2, C29.2, C30.1, C31.1, C32.1, C33.1, C34.1, C38.2, C39.2, C40.2, C41.2, C42.2, C43.2, C44.2, C45.2, C46.2, C47.2, C48.2, C49.2, C50.2, C51.2, C52.2, C53.2, C54.2, C55.2, C56.2, C57.2, C58.2, C59.2, C60.2, C61.2, C62.2, C63.2, C64.2, C65.2, D1.1, D5.3, D6.3, D7.3, D8.3, D9.3, D11.2 (A), D12.2 (A), D13.1 (A), D14.1 (A), J1.3, J1.5, J1.9, JP1.1 (A), P1.0, P1.A1 (GND), P1.A12 (GND), P1.B1 (GND), P1.B12 (GND), Q3.2 (E), R1.1, R2.1, R6.1, R14.2, R16.2, R27.1, U1.2 (GND), U3.4 (GND), U3.5, U3.6, U6.6 (GND), U6.9 (POWERPAD), U7.6 (VSS), U7.12 (VSS), U7.14 (VSSSMPS), U7.18 (VSS), U7.21 (PF7), U7.22 (PF8), U7.24 (PF10), U7.33 (VSS), U7.34 (VSSA), U7.41 (VSS), U7.55 (VSS), U7.69 (VSS), U7.80 (VSS), U7.89 (VSS), U7.104 (VSS), U7.118 (VSS), U7.128 (VSS), U7.141 (VSS), U8.2 (GND), U8.9 (GND), U9.2 (GND), U9.9 (GND), U10.2 (GND), U10.9 (GND), U11.2 (GND), U11.9 (GND), U12.4 (EN), U12.5 (GND), U12.6 (GND), U12.7 (GND), U12.8 (GND), U13.2 (GND), Y1.2, Y1.4
GREEN-: R18.2, U5.3 (G-)
HSE_IN: C23.1, U7.25 (PH0), Y1.1
HSE_OUT: C24.1, U7.26 (PH1), Y1.3
L4: C37.2, D12.1 (K), L4.1, U6.8 (PH)
LED_BLUE: R17.1, U7.1 (PE2)
LED_GREEN: R18.1, U7.2 (PE3)
LED_RED: R19.1, U7.3 (PE4)
NRST: C38.1, J1.10, U7.27 (NRST)
unnamed: D11.1 (K), L3.1, U12.2 (OUT)
unnamed: D2.2 (A), D15.2 (A), Q4.4 (G), R1.2
unnamed: JP1.2 (B), U7.23 (PF9)
unnamed: Q3.3 (C), R26.1, U1.4 (EN)
unnamed: R9.2, U1.3 (FLG)
unnamed: R27.2, U1.5 (ISET)
unnamed: C37.1, U6.1 (BOOT)
RED-: R19.2, U5.2 (R-)
SBU1: D5.1, P1.A8 (SUB1), Q2.3 (C), R24.2, R28.1
SBU1_ADC: D13.3 (COM), R28.2, U7.47 (PC4)
SBU2: D5.2, P1.B8 (SUB2), Q1.3 (C), R23.2, R29.1
SBU2_ADC: D14.3 (COM), R29.2, U7.38 (PA1)
SWCLK: J1.4, U7.107 (PA14(JTCK)
SWDIO: J1.2, U7.102 (PA13(JTMS)
USB_D+: R21.2, U7.101 (PA12)
USB_D-: R20.1, U7.100 (PA11)
USB_LOAD: Q3.1 (B), U7.74 (PB14)
USB_PWR: C17.2, C34.2, D10.2 (A), U1.1 (OUT), U3.1 (VCC), U13.5 (VBUS)
USB_R_D+: R21.1, U3.3 (D+), U13.3 (I/O2), U13.4 (I/O2)
USB_R_D-: R20.2, U3.2 (D-), U13.1 (I/O1), U13.6 (I/O1)
VCAP: C39.1, C40.1, C42.1, C64.1, L5.2, U7.17 (VFBSMPS), U7.68 (VCAP), U7.103 (VCAP), U7.140 (VCAP)
VDDA: C43.1, C44.1, FB1.1, U7.35 (VREF+), U7.36 (VDDA)
VLXSMPS: C41.1, L5.1, U7.15 (VLXSMPS)
VSENSE: R5.1, R6.2, U6.4 (VSENSE)
VoltageSens: R2.2, R3.1, U7.52 (PF11)
relay_SBU1: Q2.1 (B), U7.109 (PC10)
relay_SBU2: Q1.1 (B), U7.110 (PC11)

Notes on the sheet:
USB Connector
CAN Interface
5V to 3.3V Regulator
OBD-C Connector
Decoupling capacitors
Power Regulators
12V to 5V Regulator
Microcontroller
Ignition / SBU Detection
Reverse polarity protection
HSE 25 MHz
BOOT0
NRST
SWD (ARM 10-pin)
VCAP
SMPS step-down
VDDA filter
LED drivers (PE4/PE3/PE2, active low)
SBU ADC conditioning (10k + BAT54S)
5V sense (PB1)
CAN STB pull-ups (default standby)
STM32H725 decoupling (VDD/VBAT/VDDLDO/VDDSMPS/VDD33USB)
Power flags
PCR-2: VFBSMPS ligado a VCAP (AN5419 direct SMPS)
PCR-1: JP1 fechado = RED (id1=0); aberto = HYBRID (id1=4)
Item 5 SI/PI: D15 zener 12 V limita Vgs de Q4 (K = 12V_Protected, A = gate)
Item 8 SI/PI: U13 ESD array USB (flow-through: lado conector pinos 1/3, lado MCU pinos 6/4)

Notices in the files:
README.md:
Credits and licenses:
- comma.ai: [panda](https://github.com/commaai/panda), [openpilot](https://github.com/commaai/openpilot),
[opendbc](https://github.com/commaai/opendbc) (MIT). The Honda City 7G support itself was
contributed upstream in commaai/opendbc #2425.
- Lukas Loetkolben: OpenpilotHardware [BlackPanda v2](https://github.com/lukasloetkolben/OpenBlackPanda)
and HarnessBox (MIT), the baseline the Hybrid Panda derives from and the hardware used by
the black panda tracks. The MIT notice is kept in the derived KiCad project.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
